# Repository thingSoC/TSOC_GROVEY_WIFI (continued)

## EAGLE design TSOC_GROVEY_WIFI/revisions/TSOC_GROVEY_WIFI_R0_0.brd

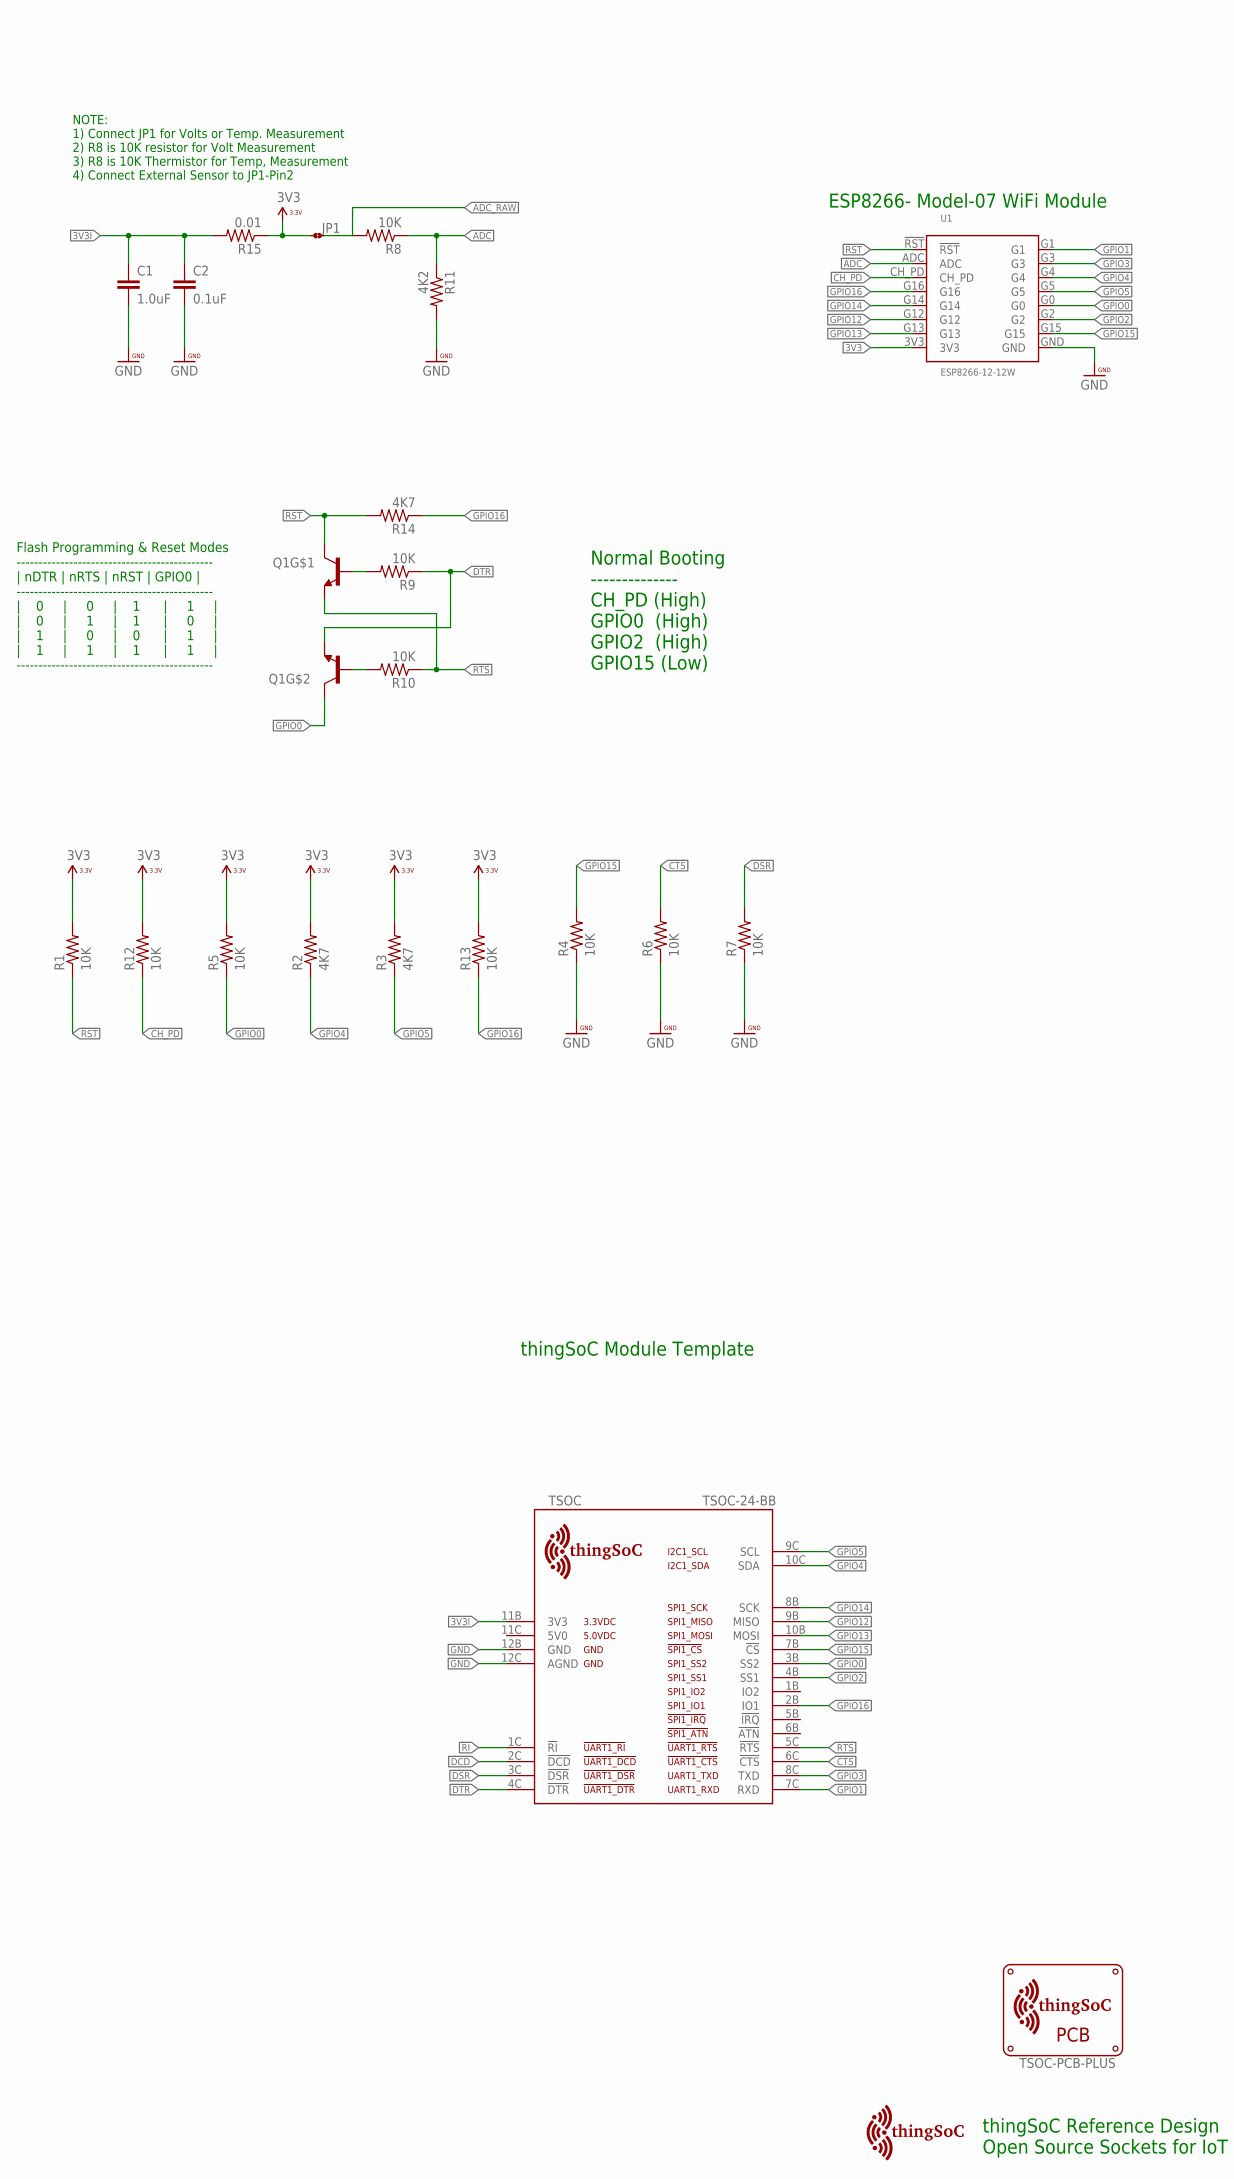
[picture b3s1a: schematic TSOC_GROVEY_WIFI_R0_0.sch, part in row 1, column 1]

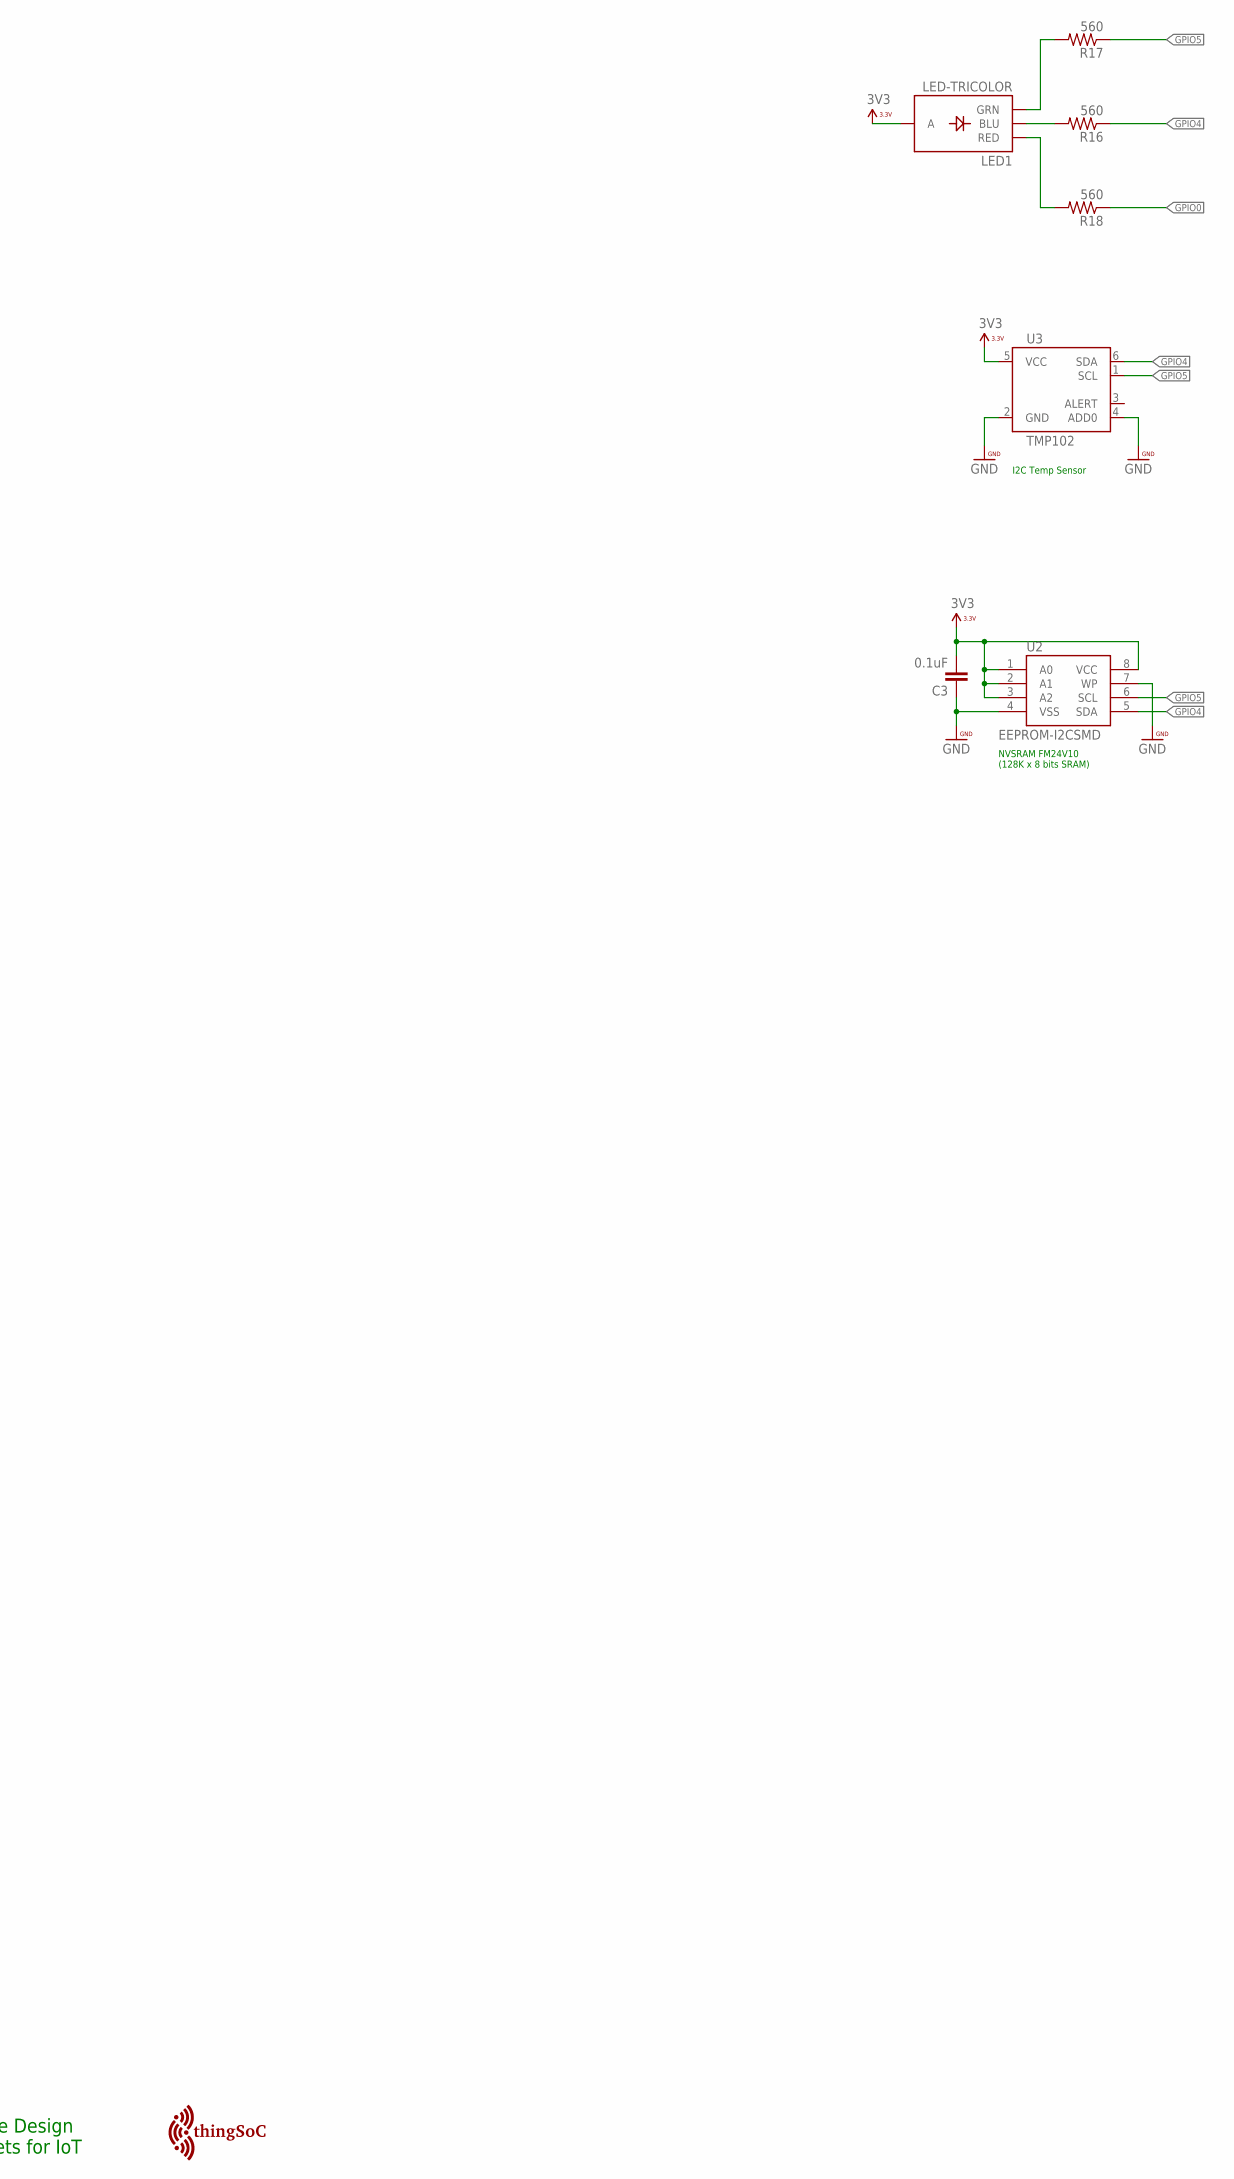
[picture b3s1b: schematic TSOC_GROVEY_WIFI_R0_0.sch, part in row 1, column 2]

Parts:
C1: 1.0uF; 0402-CAP
C2, C3: 0.1uF; 0402-CAP
JP1: JMP-2-NO-0402
LED1: LED-TRICOLOR; LED-TRICOLOR-SMD
Q1: MMBT2222A; SOT363
R1, R4, R5, R6, R7, R8, R9, R10, R12, R13: 10K; 0402-RES
R2, R3, R14: 4K7; 0402-RES
R11: 4K2; 0402-RES
R15: 0.01; 0402-RES
R16, R17, R18: 560; 0402-RES
TSOC: TSOC-24-BB; TSOC-BB-S24
U1: ESP8266-12-12W; ESP8266-12W
U2: EEPROM-I2CSMD; SO08
U3: TMP102; SOT563
U$19, U$20: TSOC-LOGO-MED
U$25: TSOC-PCB-PLUS; TSOC-BB-BRD-PLUS-DIM

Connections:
3V3: C3.2, JP1.1, LED1.A, R1.2, R2.2, R3.2, R5.2, R12.2, R13.2, R15.1, U1.3V3, U2.1 (A0), U2.2 (A1), U2.3 (A2), U2.8 (VCC), U3.5 (VCC)
3V3I: C1.1, C2.1, R15.2, TSOC.11B (3V3)
!CTS: R6.2, TSOC.6C (!CTS)
!DCD: TSOC.2C (!DCD)
!DSR: R7.2, TSOC.3C (!DSR)
!DTR: Q1.1 (E), R9.1, TSOC.4C (!DTR)
!RI: TSOC.1C (!RI)
!RST: Q1.3 (C), R1.1, R14.2, U1.!RST
!RTS: Q1.4 (E), R10.1, TSOC.5C (!RTS)
ADC: R8.1, R11.1, U1.ADC
ADC_RAW: JP1.2, R8.2
BLU: LED1.B (BLU), R16.2
CH_PD: R12.1, U1.CH_PD
GND: C1.2, C2.2, C3.1, R4.1, R6.1, R7.1, R11.2, TSOC.12B (GND), TSOC.12C (AGND), U1.GND, U2.4 (VSS), U2.7 (WP), U3.2 (GND), U3.4 (ADD0)
GPIO0: Q1.6 (C), R5.1, R18.1, TSOC.3B (SS2), U1.G0
GPIO1: TSOC.7C (RXD), U1.G1
GPIO2: TSOC.4B (SS1), U1.G2
GPIO3: TSOC.8C (TXD), U1.G3
GPIO4: R2.1, R16.1, TSOC.10C (SDA), U1.G4, U2.5 (SDA), U3.6 (SDA)
GPIO5: R3.1, R17.1, TSOC.9C (SCL), U1.G5, U2.6 (SCL), U3.1 (SCL)
GPIO12: TSOC.9B (MISO), U1.G12
GPIO13: TSOC.10B (MOSI), U1.G13
GPIO14: TSOC.8B (SCK), U1.G14
GPIO15: R4.2, TSOC.7B (!CS), U1.G15
GPIO16: R13.1, R14.1, TSOC.2B (IO1), U1.G16
GRN: LED1.G (GRN), R17.2
unnamed: Q1.5 (B), R9.2
unnamed: Q1.2 (B), R10.2
RED: LED1.R (RED), R18.2

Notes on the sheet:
thingSoC Reference Design Open Source Sockets for IoT
thingSoC Module Template
Normal Booting -------------- CH_PD (High) GPIO0 (High) GPIO2 (High) GPIO15 (Low)
ESP8266- Model-07 WiFi Module
Flash Programming & Reset Modes --------------------------------------------- | nDTR | nRTS | nRST | GPIO0 | --------------------------------------------- | 0 | 0 | 1 | 1 | | 0 | 1 | 1 | 0 | | 1 | 0 | 0 | 1 | | 1 | 1 | 1 | 1 | ---------------------------------------------
NOTE: 1) Connect JP1 for Volts or Temp. Measurement 2) R8 is 10K resistor for Volt Measurement 3) R8 is 10K Thermistor for Temp, Measurement 4) Connect External Sensor to JP1-Pin2
NVSRAM FM24V10 (128K x 8 bits SRAM)
I2C Temp Sensor

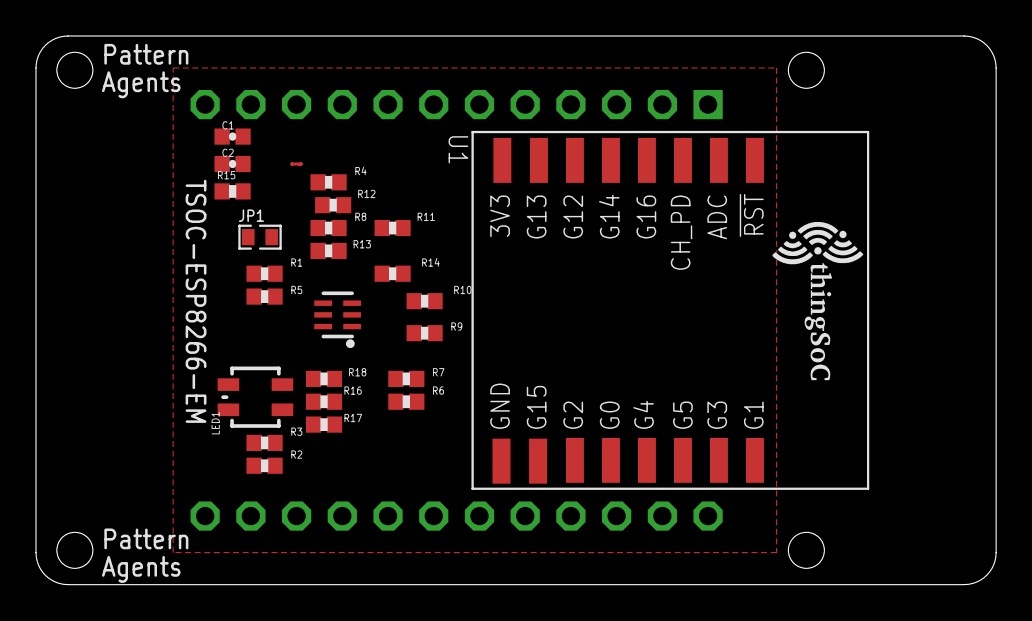
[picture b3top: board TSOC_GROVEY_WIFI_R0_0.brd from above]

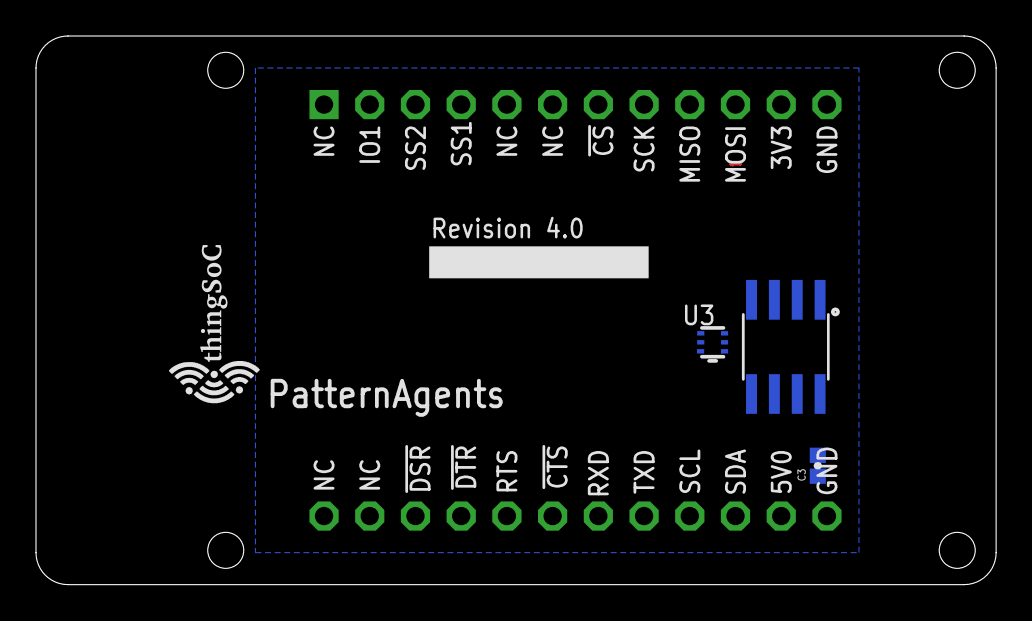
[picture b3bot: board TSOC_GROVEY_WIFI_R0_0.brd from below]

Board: 2 copper layers, 53.3 x 30.5 mm, 31 parts (4 on the bottom side), 27 nets.

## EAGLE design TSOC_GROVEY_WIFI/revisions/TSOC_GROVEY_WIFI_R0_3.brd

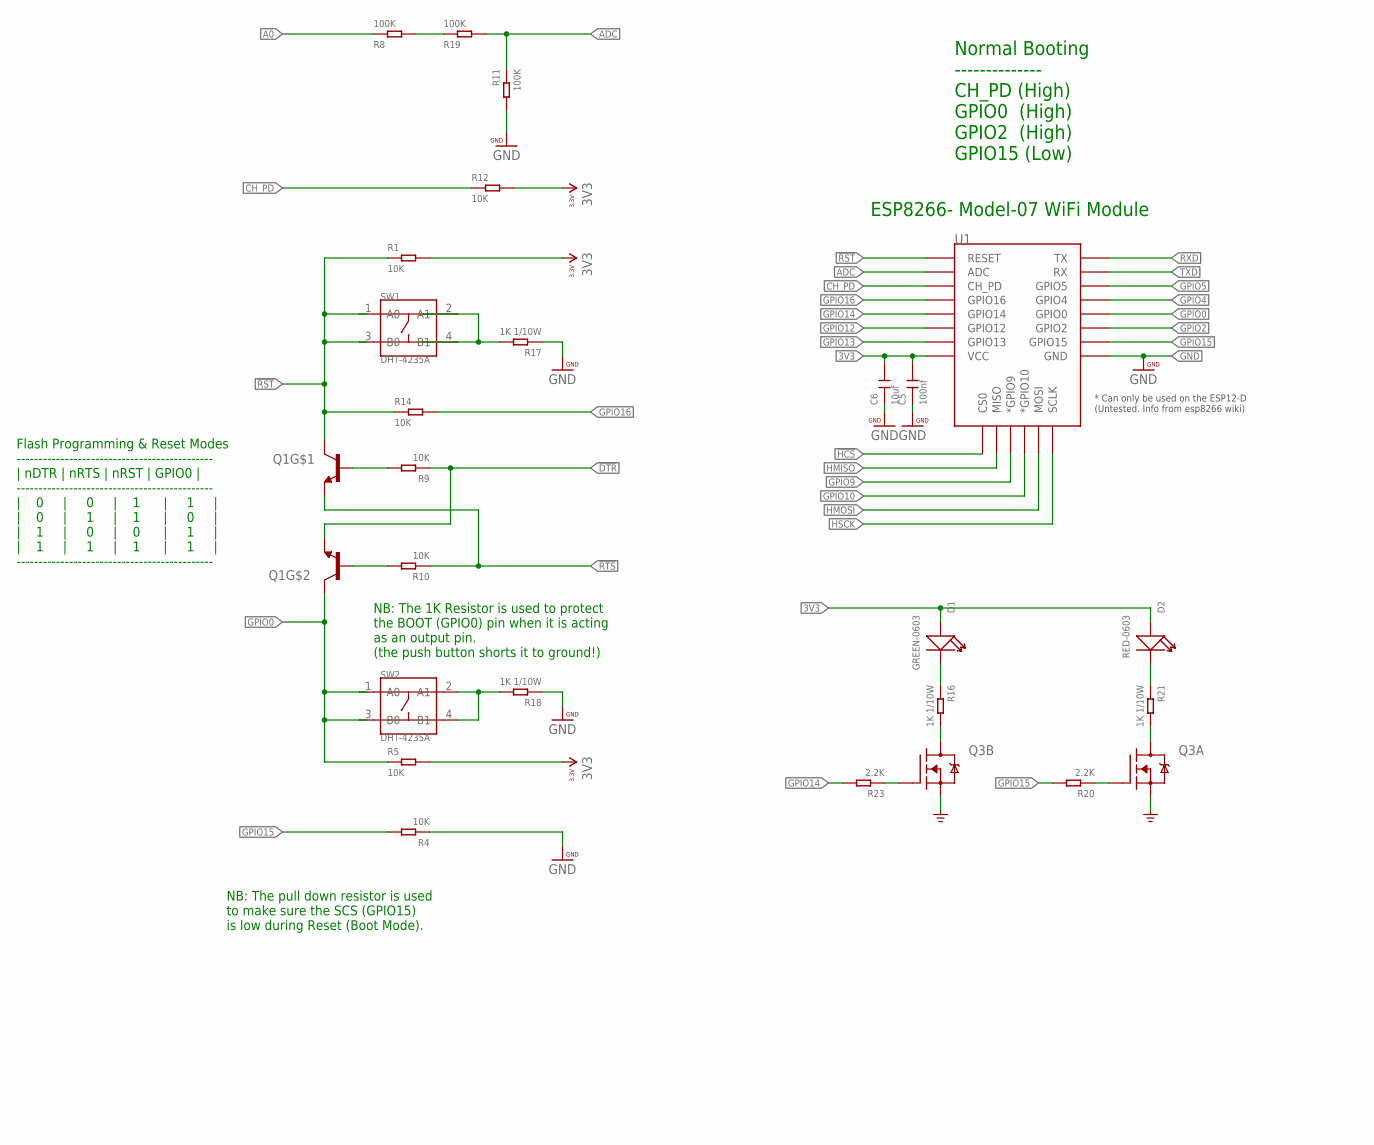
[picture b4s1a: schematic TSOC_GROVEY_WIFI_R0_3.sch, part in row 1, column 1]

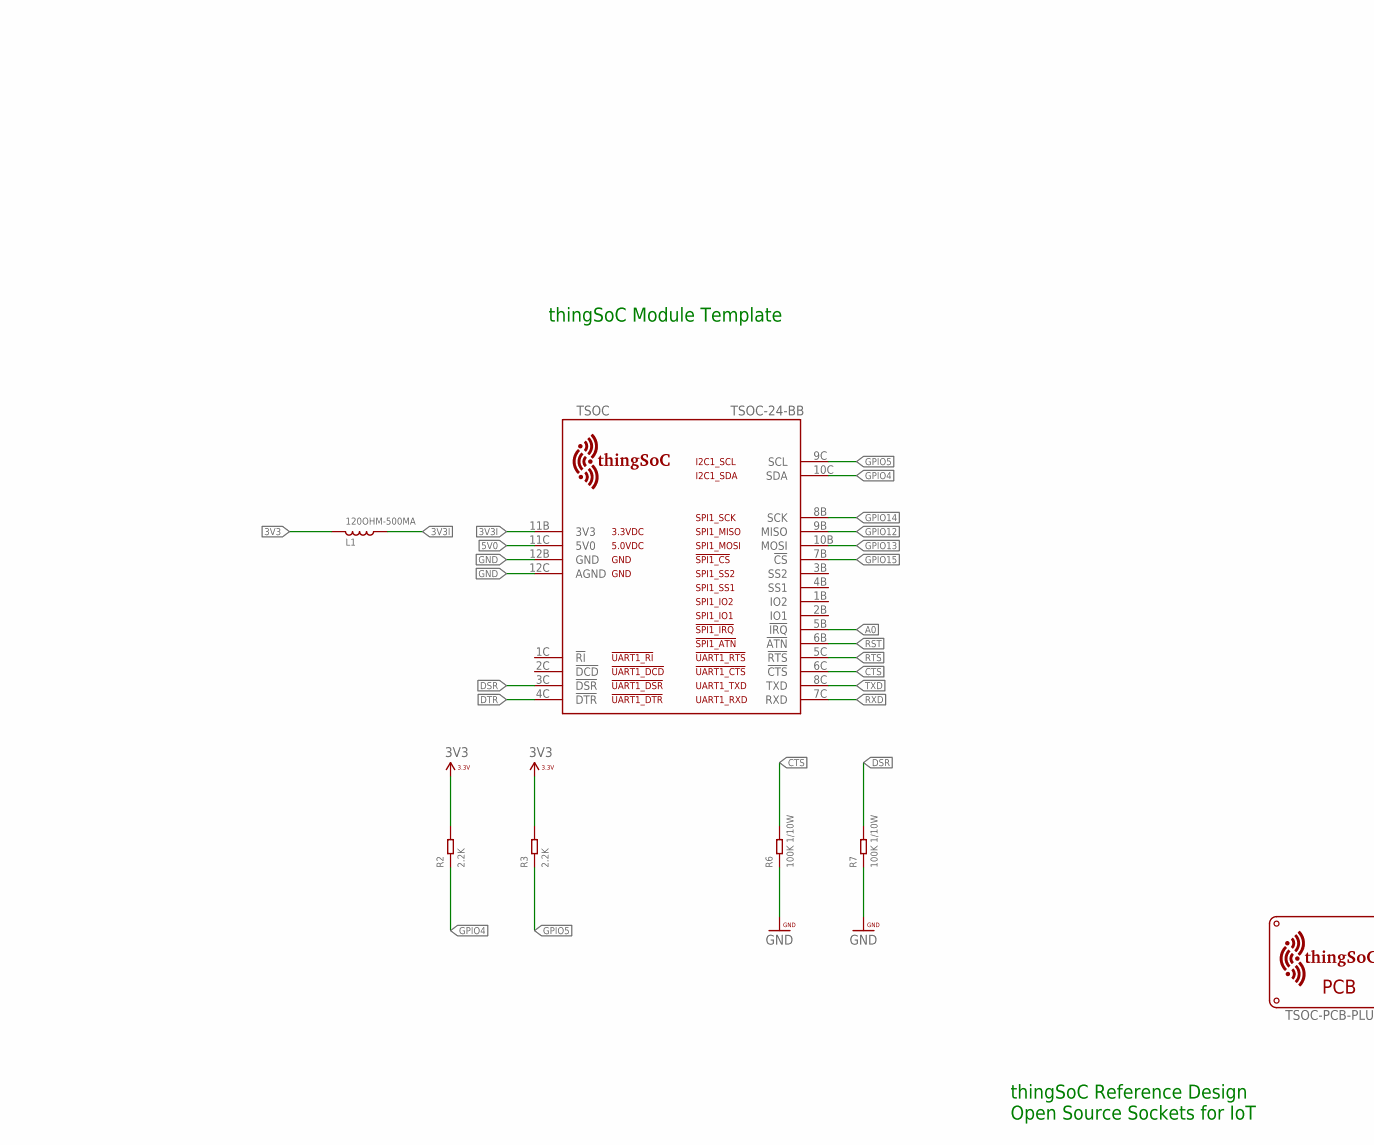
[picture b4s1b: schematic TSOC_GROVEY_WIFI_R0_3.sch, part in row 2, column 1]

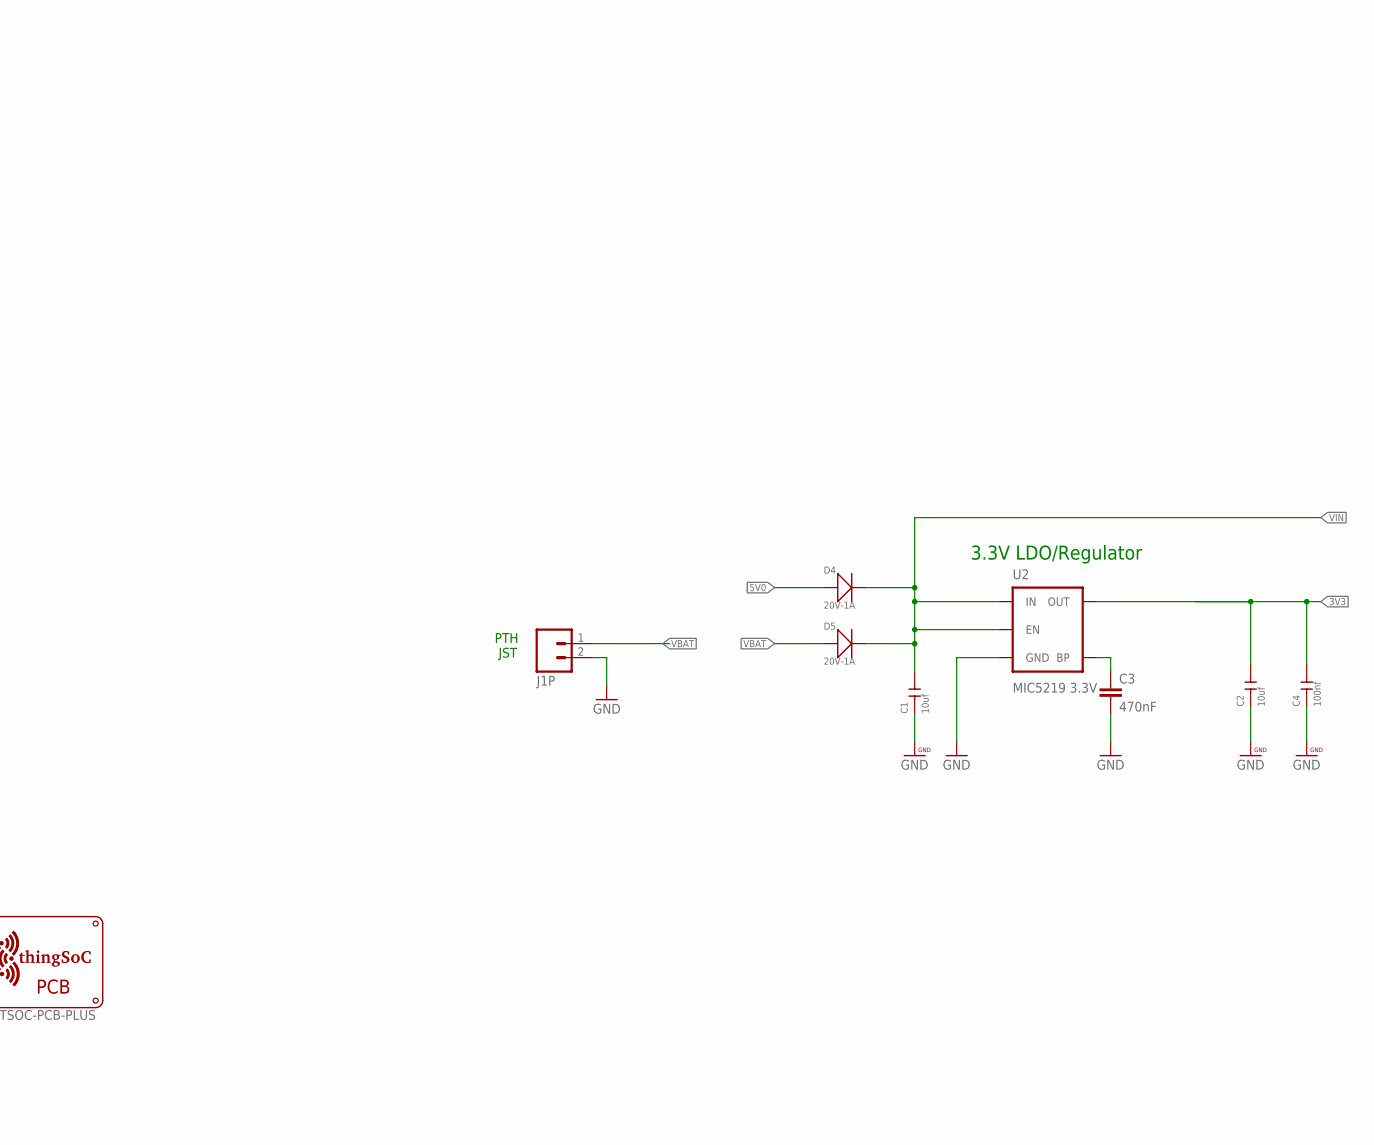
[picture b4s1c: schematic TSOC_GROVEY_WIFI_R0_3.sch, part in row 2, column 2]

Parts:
C1, C2, C6: 10uf; C1206
C3: 470nF; 0402-CAP
C4, C5: 100nf; C0603
D1: GREEN-0603; LED-0603
D2: RED-0603; LED-0603
D4, D5: 20V-1A; SOD-123
J1P: M02-JST-2-PTH-NO_SILK; JST-2-PTH-NS
L1: 120OHM-500MA; L0603
PCB: TSOC-PCB-PLUS; TSOC-BB-BRD-PLUS-DIM
Q1: MMBT2222A; SOT363
Q3: FDG1024NZ; SOT95P280X110-6N
R1, R4, R5, R9, R10, R12, R14: 10K; R0603
R2, R3, R20, R23: 2.2K; R0603
R6, R7: 100K 1/10W; R0603
R8, R11, R19: 100K; R0603
R16, R17, R18, R21: 1K 1/10W; R0603
SW1, SW2: DHT-4235A; SW4-SMD-4.2X3.2X2.5MM
TSOC: TSOC-24-BB; TSOC-BB-S24
U1: ESP12ESMD; ESP12E-SMD
U2: MIC5219 3.3V; SOT23-5

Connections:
3V3: C2.2, C4.2, C5.2, C6.2, D1.+, D2.+, L1.1, R1.2, R2.2, R3.2, R5.2, R12.2, U1.VCC, U2.5 (OUT)
3V3I: L1.2, TSOC.11B (3V3)
5V0: D4.+, TSOC.11C (5V0)
!BOOTPD: R18.2, SW2.2 (A1), SW2.4 (B1)
!CTS: R6.2, TSOC.6C (!CTS)
!DCDG: Q3.2 (G), R20.1
!DSR: R7.2, TSOC.3C (!DSR)
!DTR: Q1.1 (E), R9.1, TSOC.4C (!DTR)
!HCS: U1.CS0
!RST: Q1.3 (C), R1.1, R14.1, SW1.1 (A0), SW1.3 (B0), TSOC.6B (!ATN), U1.RESET
!RSTPD: R17.2, SW1.2 (A1), SW1.4 (B1)
!RTS: Q1.4 (E), R10.1, TSOC.5C (!RTS)
!SCSG: Q3.5 (G), R23.1
A0: R8.1, TSOC.5B (!IRQ)
ADC: R11.1, R19.2, U1.ADC
ADC2: R8.2, R19.1
BYPASS1: C3.1, U2.4 (BP)
CH_PD: R12.1, U1.CH_PD
G0: Q3.6 (D), R21.2
G15: Q3.3 (D), R16.2
GND: C1.1, C2.1, C3.2, C4.1, C5.1, C6.1, J1P.2, Q3.1 (S), Q3.4 (S), R4.1, R6.1, R7.1, R11.2, R17.1, R18.1, TSOC.12B (GND), TSOC.12C (AGND), U1.GND, U2.2 (GND)
GPIO0: Q1.6 (C), R5.1, SW2.1 (A0), SW2.3 (B0), U1.GPIO0
GPIO2: U1.GPIO2
GPIO4: R2.1, TSOC.10C (SDA), U1.GPIO4
GPIO5: R3.1, TSOC.9C (SCL), U1.GPIO5
GPIO9: U1.GPIO9 (*GPIO9)
GPIO10: U1.GPIO10 (*GPIO10)
GPIO12: TSOC.9B (MISO), U1.GPIO12
GPIO13: TSOC.10B (MOSI), U1.GPIO13
GPIO14: R23.2, TSOC.8B (SCK), U1.GPIO14
GPIO15: R4.2, R20.2, TSOC.7B (!CS), U1.GPIO15
GPIO16: R14.2, U1.GPIO16
HMISO: U1.MISO
HMOSI: U1.MOSI
HSCK: U1.SCLK
LED1: D1.-, R16.1
LED2: D2.-, R21.1
RES: Q1.5 (B), R9.2
ROS: Q1.2 (B), R10.2
RXD: TSOC.7C (RXD), U1.TXD0 (TX)
TXD: TSOC.8C (TXD), U1.RXD0 (RX)
VBAT: D5.+, J1P.1
VIN: C1.2, D4.-, D5.-, U2.1 (IN), U2.3 (EN)

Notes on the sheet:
thingSoC Reference Design Open Source Sockets for IoT
thingSoC Module Template
Normal Booting -------------- CH_PD (High) GPIO0 (High) GPIO2 (High) GPIO15 (Low)
ESP8266- Model-07 WiFi Module
Flash Programming & Reset Modes --------------------------------------------- | nDTR | nRTS | nRST | GPIO0 | --------------------------------------------- | 0 | 0 | 1 | 1 | | 0 | 1 | 1 | 0 | | 1 | 0 | 0 | 1 | | 1 | 1 | 1 | 1 | ---------------------------------------------
NB: The 1K Resistor is used to protect the BOOT (GPIO0) pin when it is acting as an output pin. (the push button shorts it to ground!)
NB: The pull down resistor is used to make sure the SCS (GPIO15) is low during Reset (Boot Mode).
PTH JST
3.3V LDO/Regulator

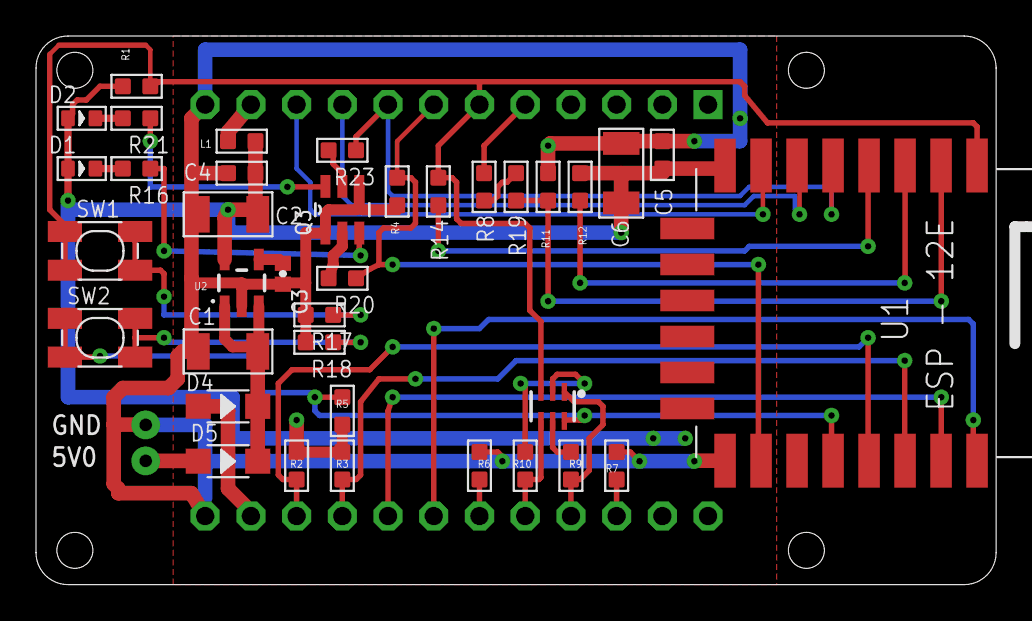
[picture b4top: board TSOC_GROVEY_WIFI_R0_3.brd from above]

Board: 2 copper layers, 53.3 x 30.5 mm, 40 parts (0 on the bottom side), 36 nets.

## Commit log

2016-09-03 initial version
